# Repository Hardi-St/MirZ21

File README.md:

# MirZ21
Märklin infrared to Z21 bridge

Attention: The program is NOT released yet

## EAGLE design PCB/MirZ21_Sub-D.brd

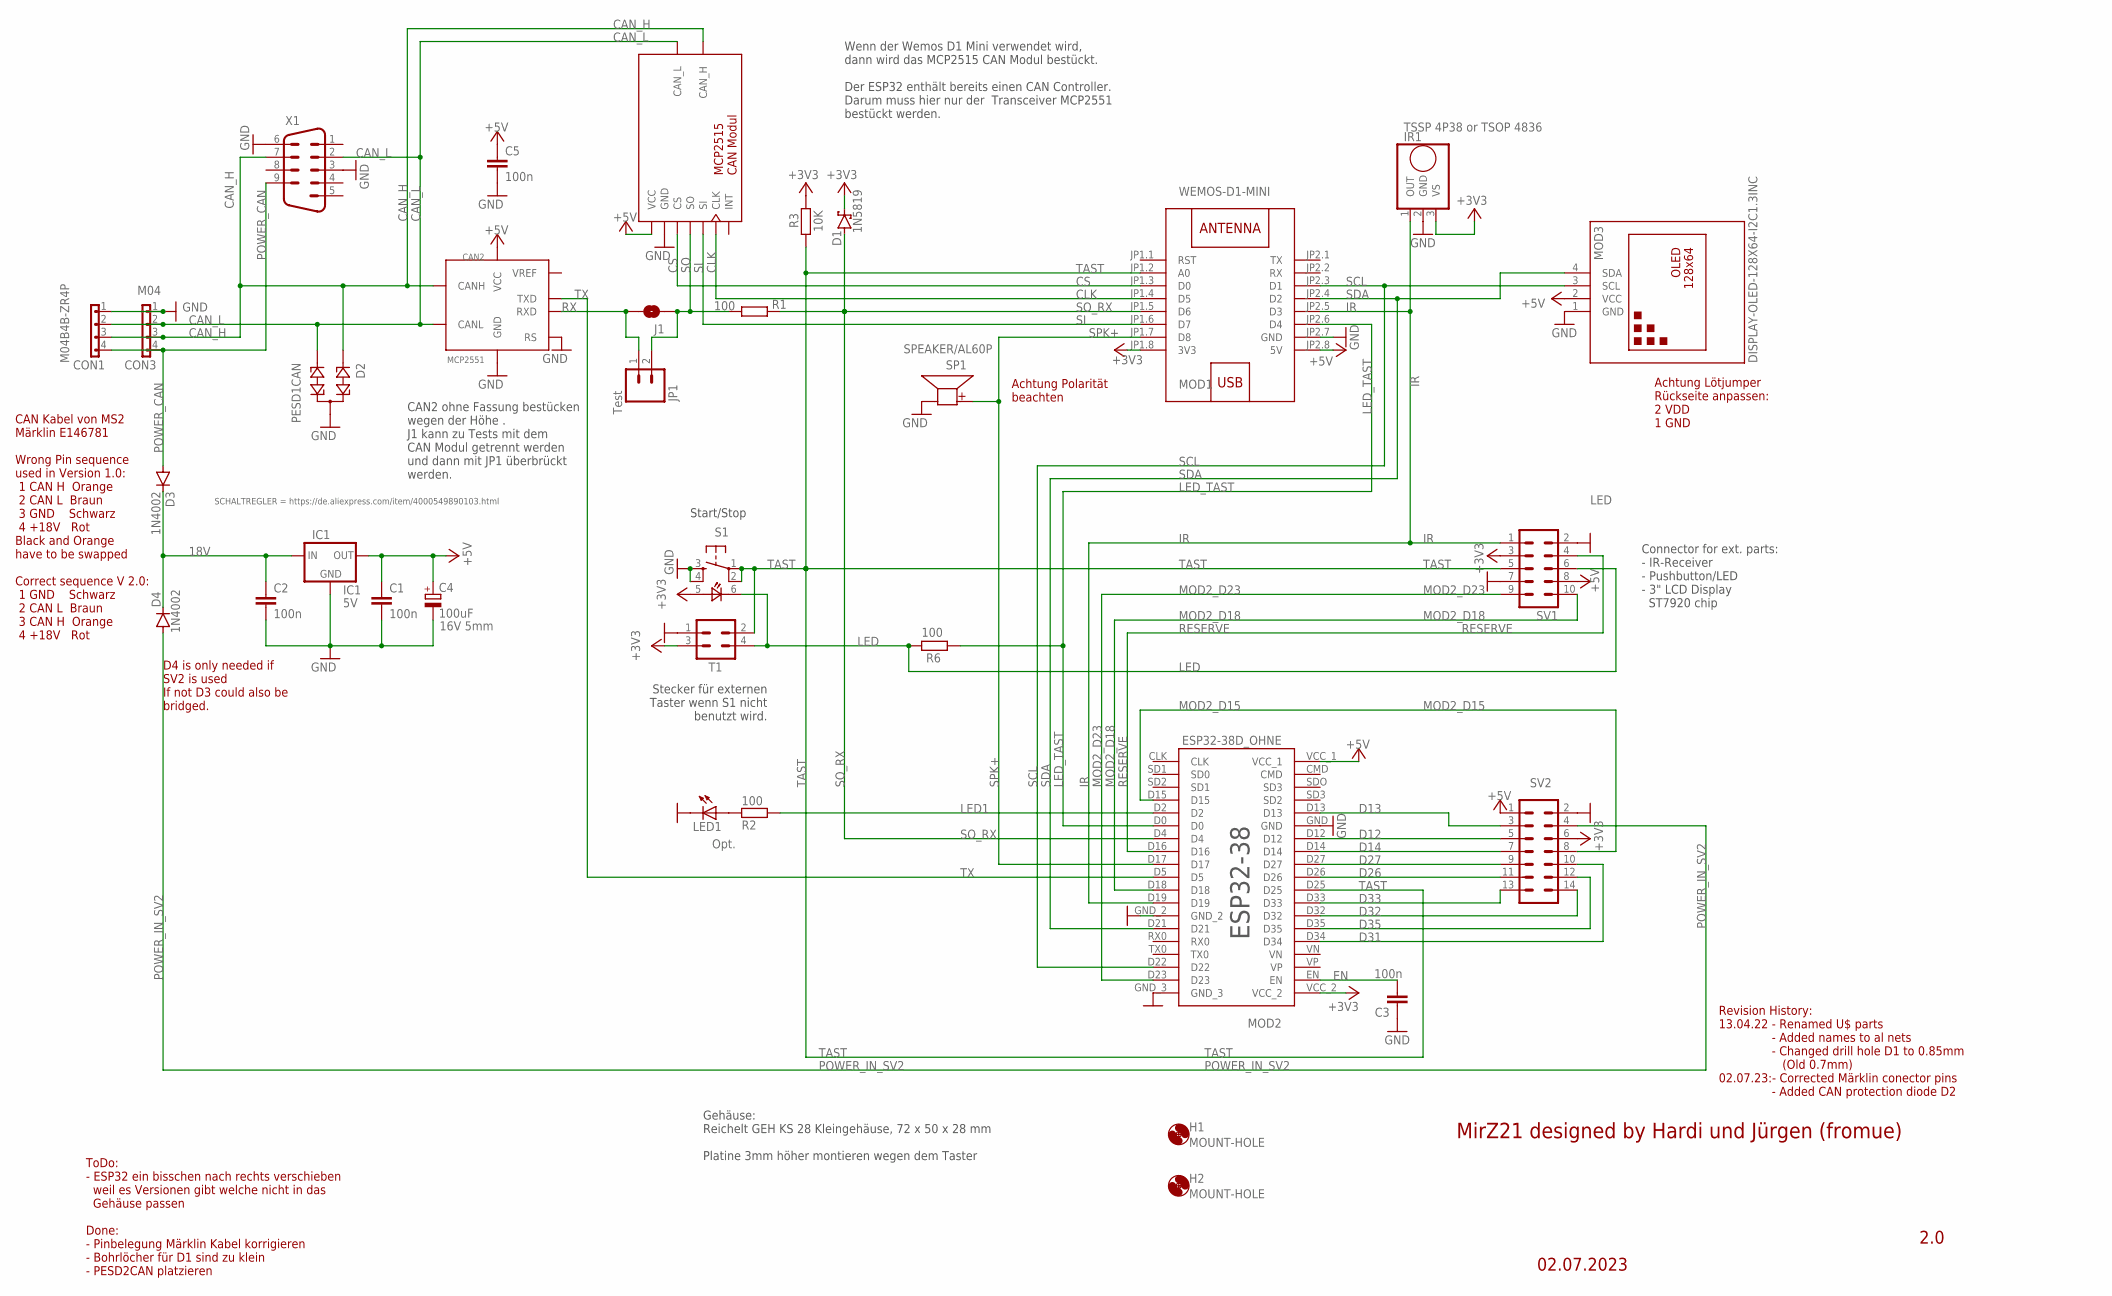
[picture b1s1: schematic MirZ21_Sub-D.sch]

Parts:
C1, C2, C3, C5: 100n; C025-025X050
C4: 100uF; TT2D5L
CAN1: MCP2515_CAN_CUTCUT; MCP2515_CAN_CUT
CAN2: MCP2551; DIP08
CON1: M04B4B-ZR4P; B4B-ZR4P
CON3: M04; 1X04
D1: 1N5819; DO41-7.6
D2: PESD1CAN; SOT23
D3, D4: 1N4002; DO41-10
H1, H2: MOUNT-HOLE; GEH_KS
IC1: 5V; HX1314G
IR1: TSSP 4P38 or TSOP 4836; TSSP4P38
J1: SOLDERJUMPERTRACE; SJ_2S-TRACE
JP1: Test; 1X02
LED1: Opt.; LED3MM
MOD1: WEMOS-D1-MINI
MOD2: ESP32-38D_OHNE; ESP32-38D_0
MOD3: DISPLAY-OLED-128X64-I2C1.3INC; DISPLAY-OLED-128X64-I2C-1.3
R1, R6: 100; 0204/7
R2: 100; 0207/2V
R3: 10K; 0204/7
S1: TASTER_LEDTC-1198-B; TASTER_LED
SP1: SPEAKER/AL60P; RMP-14SP
SV1: ML10
SV2: ML14
T1: CON-HARTING-ML_ML4ML4_FEMALE; ML_ML4_FEMALE
X1: M09D

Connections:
18V: C2.1, D3.C, D4.C, IC1.IN
+3V3: D1.C, IR1.3 (VS), MOD1.JP1.8 (3V3), MOD2.VCC_2, R3.2, S1.5 (+), SV1.3, SV2.6, T1.3
+5V: C1.1, C4.+, C5.1, CAN1.1 (VCC), CAN2.3 (VCC), IC1.OUT, MOD1.JP2.8 (5V), MOD2.VCC_1, MOD3.2 (VCC), SV1.8, SV2.1
CAN_H: CAN1.9 (CAN_H), CAN2.7 (CANH), CON1.3, CON3.3, D2.1, X1.7
CAN_L: CAN1.8 (CAN_L), CAN2.6 (CANL), CON1.2, CON3.2, D2.2, X1.2
CLK: CAN1.6 (CLK), MOD1.JP1.4 (D5)
CS: CAN1.3 (CS), MOD1.JP1.3 (D0)
D12: MOD2.D12, SV2.5
D13: MOD2.D13, SV2.3
D14: MOD2.D14, SV2.7
D26: MOD2.D26, SV2.11
D27: MOD2.D27, SV2.9
D31: MOD2.D34, SV2.10
D32: MOD2.D32, SV2.14
D33: MOD2.D33, SV2.13
D35: MOD2.D35, SV2.12
EN: C3.2, MOD2.EN
GND: C1.2, C2.2, C3.1, C4.-, C5.2, CAN1.2 (GND), CAN2.2 (GND), CAN2.8 (RS), CON1.1, CON3.1, D2.3, IC1.GND, IR1.2 (GND), LED1.K (C), MOD1.JP2.7 (GND), MOD2.GND, MOD2.GND_2, MOD2.GND_3, MOD3.1 (GND), S1.3 (S), S1.4 (S1), SP1.2 (-), SV1.2, SV1.7, SV2.2, T1.1, X1.3, X1.6
IR: IR1.1 (OUT), MOD1.JP2.5 (D3), MOD2.D19, SV1.1
LED: R6.2, S1.6 (-), SV1.6, T1.4
LED1: MOD2.D2, R2.2
LED_TAST: MOD1.JP2.6 (D4), MOD2.D0, R6.1
MOD2_D15: MOD2.D15, SV2.8
MOD2_D18: MOD2.D18, SV1.10
MOD2_D23: MOD2.D23, SV1.9
unnamed: LED1.A, R2.1
POWER_CAN: CON1.4, CON3.4, D3.A, X1.9
POWER_IN_SV2: D4.A, SV2.4
RESERVE: MOD2.D16, SV1.4
RX: CAN2.4 (RXD), J1.2, JP1.1
SCL: MOD1.JP2.3 (D1), MOD2.D22, MOD3.3 (SCL)
SDA: MOD1.JP2.4 (D2), MOD2.D21, MOD3.4 (SDA)
SI: CAN1.5 (SI), MOD1.JP1.6 (D7)
SO: CAN1.4 (SO), J1.1, JP1.2, R1.2
SO_RX: D1.A, MOD1.JP1.5 (D6), MOD2.D4, R1.1
SPK+: MOD1.JP1.7 (D8), MOD2.D17, SP1.1 (+)
TAST: MOD1.JP1.2 (A0), MOD2.D25, R3.1, S1.1, S1.2 (P1), SV1.5, T1.2
TX: CAN2.1 (TXD), MOD2.D5
VREF: CAN2.5 (VREF)

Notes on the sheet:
Achtung Polarität beachten
02.07.2023
2.0
MirZ21 designed by Hardi und Jürgen (fromue)
Start/Stop
Gehäuse: Reichelt GEH KS 28 Kleingehäuse, 72 x 50 x 28 mm Platine 3mm höher montieren wegen dem Taster
Connector for ext. parts: - IR-Receiver - Pushbutton/LED - 3" LCD Display ST7920 chip
Wenn der Wemos D1 Mini verwendet wird, dann wird das MCP2515 CAN Modul bestückt. Der ESP32 enthält bereits einen CAN Controller. Darum muss hier nur der Transceiver MCP2551 bestückt werden.
Achtung Lötjumper Rückseite anpassen: 2 VDD 1 GND
CAN2 ohne Fassung bestücken wegen der Höhe . J1 kann zu Tests mit dem CAN Modul getrennt werden und dann mit JP1 überbrückt werden.
Stecker für externen Taster wenn S1 nicht benutzt wird.
IC1
D4 is only needed if SV2 is used If not D3 could also be bridged.
Revision History: 13.04.22 - Renamed U$ parts - Added names to al nets - Changed drill hole D1 to 0.85mm (Old 0.7mm) 02.07.23:- Corrected Märklin conector pins - Added CAN protection diode D2
ToDo: - ESP32 ein bisschen nach rechts verschieben weil es Versionen gibt welche nicht in das Gehäuse passen Done: - Pinbelegung Märklin Kabel korrigieren - Bohrlöcher für D1 sind zu klein - PESD2CAN platzieren
CAN Kabel von MS2 Märklin E146781 Wrong Pin sequence used in Version 1.0: 1 CAN H Orange 2 CAN L Braun 3 GND Schwarz 4 +18V Rot Black and Orange have to be swapped Correct sequence V 2.0: 1 GND Schwarz 2 CAN L Braun 3 CAN H Orange 4 +18V Rot

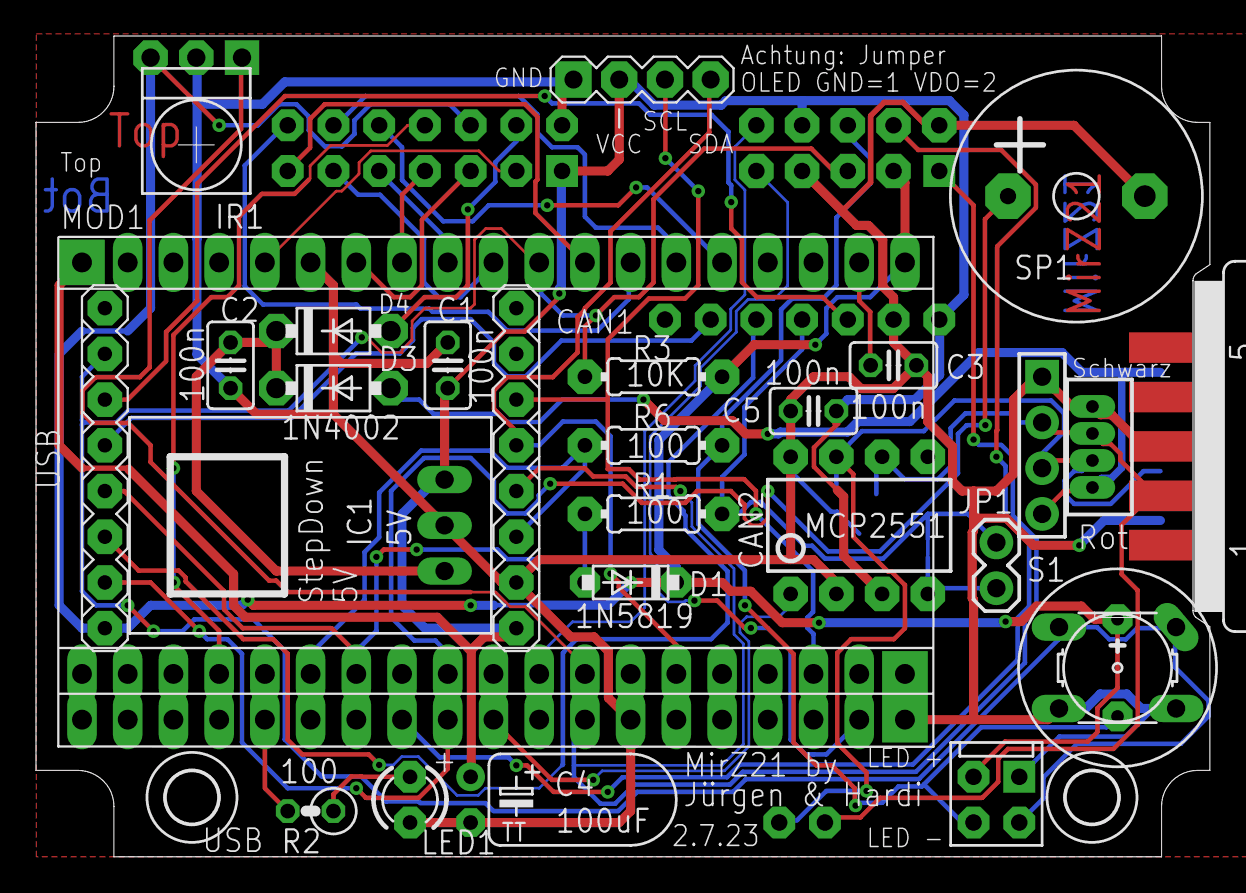
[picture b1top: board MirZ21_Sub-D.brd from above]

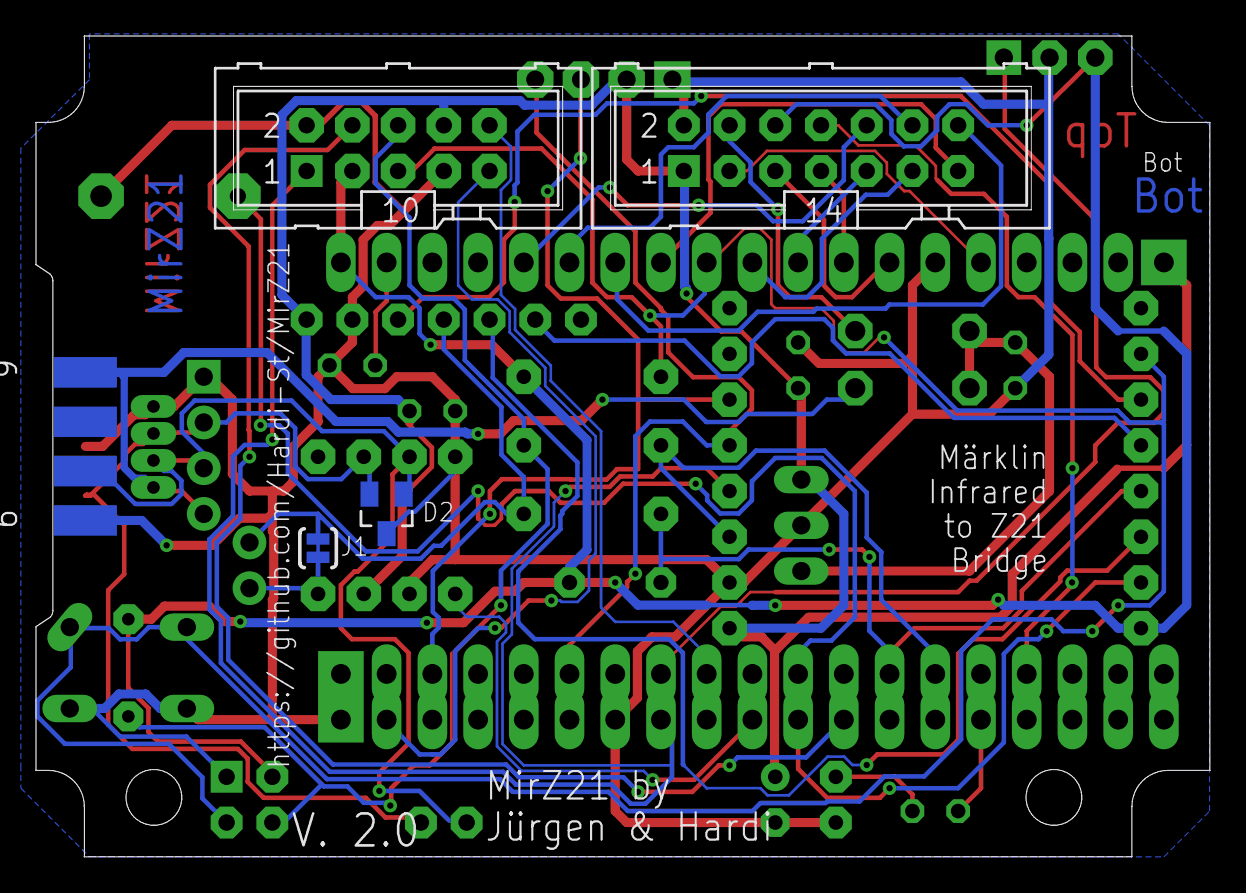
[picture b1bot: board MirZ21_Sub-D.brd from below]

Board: 2 copper layers, 65.2 x 45.6 mm, 33 parts (4 on the bottom side), 38 nets.

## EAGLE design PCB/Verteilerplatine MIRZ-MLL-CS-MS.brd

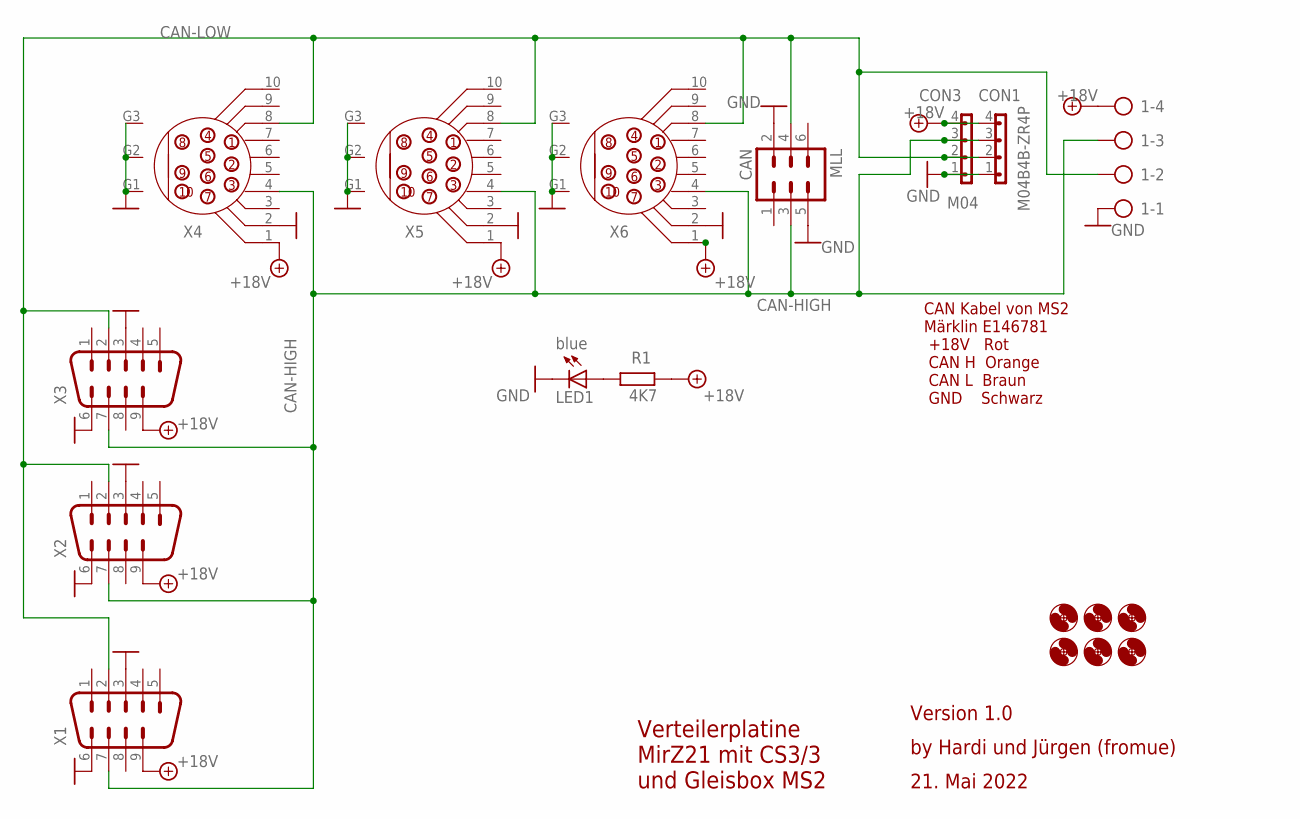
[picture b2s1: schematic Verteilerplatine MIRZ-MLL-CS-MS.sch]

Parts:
1: CAN-LOW; AK500/4-H
CON1: M04B4B-ZR4P; B4B-ZR4P
CON3: M04; 1X04
H1, H2, H3, H4, H5, H6: MOUNT-HOLE3.0; 3,0
LED1: blue; LED3MM
MLL: CAN; ML6
R1: 4K7; 0204/7
X1, X2, X3: M09V
X4, X5, X6: MDSSV-BC10; SSV-BC10

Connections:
+18V: 1.4, CON1.4, CON3.4, R1.2, X1.9, X2.9, X3.9, X4.1, X5.1, X6.1
CAN-HIGH: 1.3, CON1.3, CON3.3, MLL.3, X1.7, X2.7, X3.7, X4.4, X5.4, X6.4
CAN-LOW: 1.2, CON1.2, CON3.2, MLL.4, X1.2, X2.2, X3.2, X4.8, X5.8, X6.8
GND: 1.1, CON1.1, CON3.1, LED1.K (C), MLL.2, MLL.5, X1.3, X1.6, X2.3, X2.6, X3.3, X3.6, X4.2, X4.G1 (GND1), X4.G2 (GND2), X4.G3 (GND3), X5.2, X5.G1 (GND1), X5.G2 (GND2), X5.G3 (GND3), X6.2, X6.G1 (GND1), X6.G2 (GND2), X6.G3 (GND3)
unnamed: LED1.A, R1.1

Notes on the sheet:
CAN Kabel von MS2 Märklin E146781 +18V Rot CAN H Orange CAN L Braun GND Schwarz
Verteilerplatine MirZ21 mit CS3/3 und Gleisbox MS2
by Hardi und Jürgen (fromue)
Version 1.0
21. Mai 2022

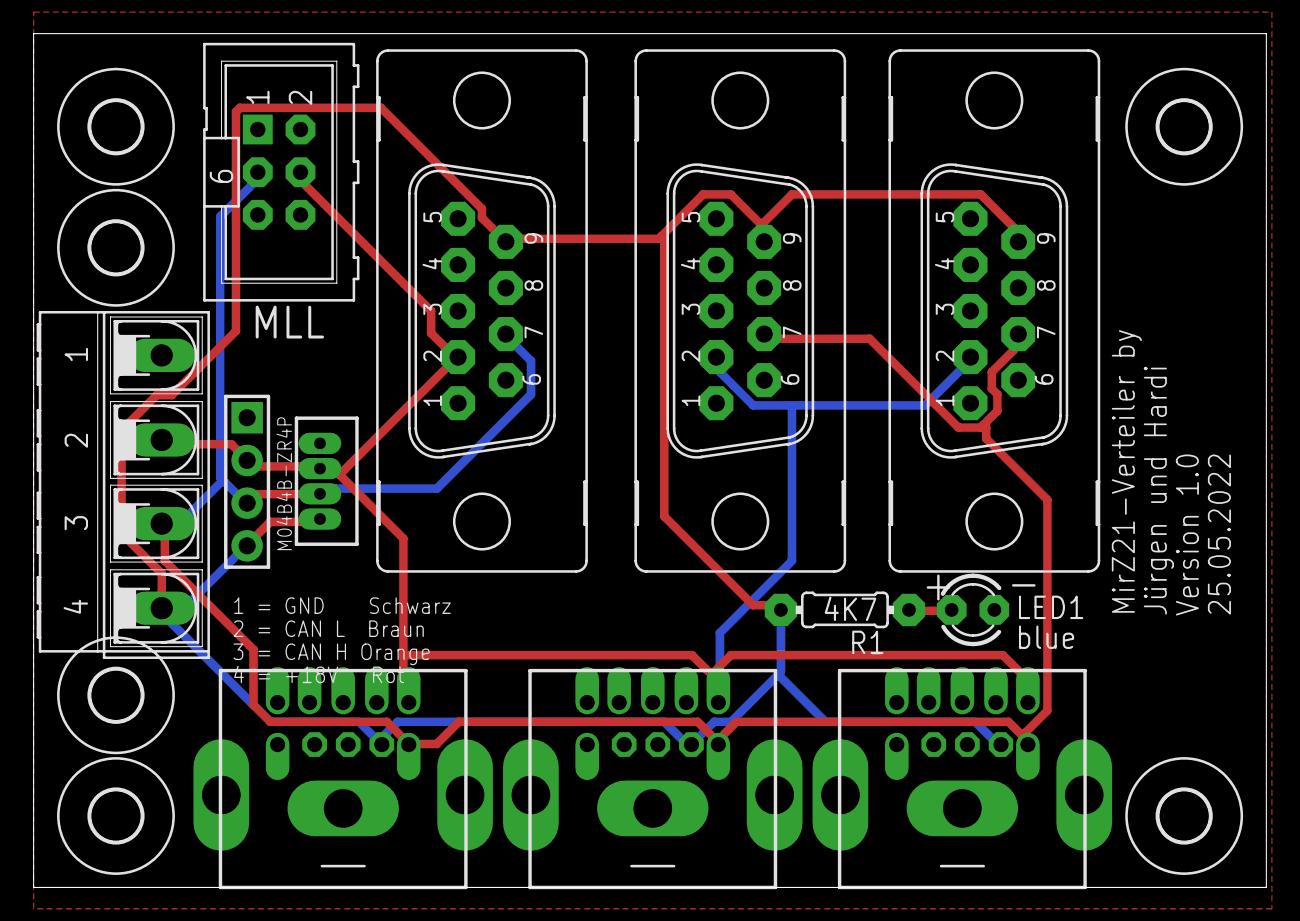
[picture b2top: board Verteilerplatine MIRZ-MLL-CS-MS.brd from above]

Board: 2 copper layers, 73.3 x 50.8 mm, 18 parts (0 on the bottom side), 5 nets.

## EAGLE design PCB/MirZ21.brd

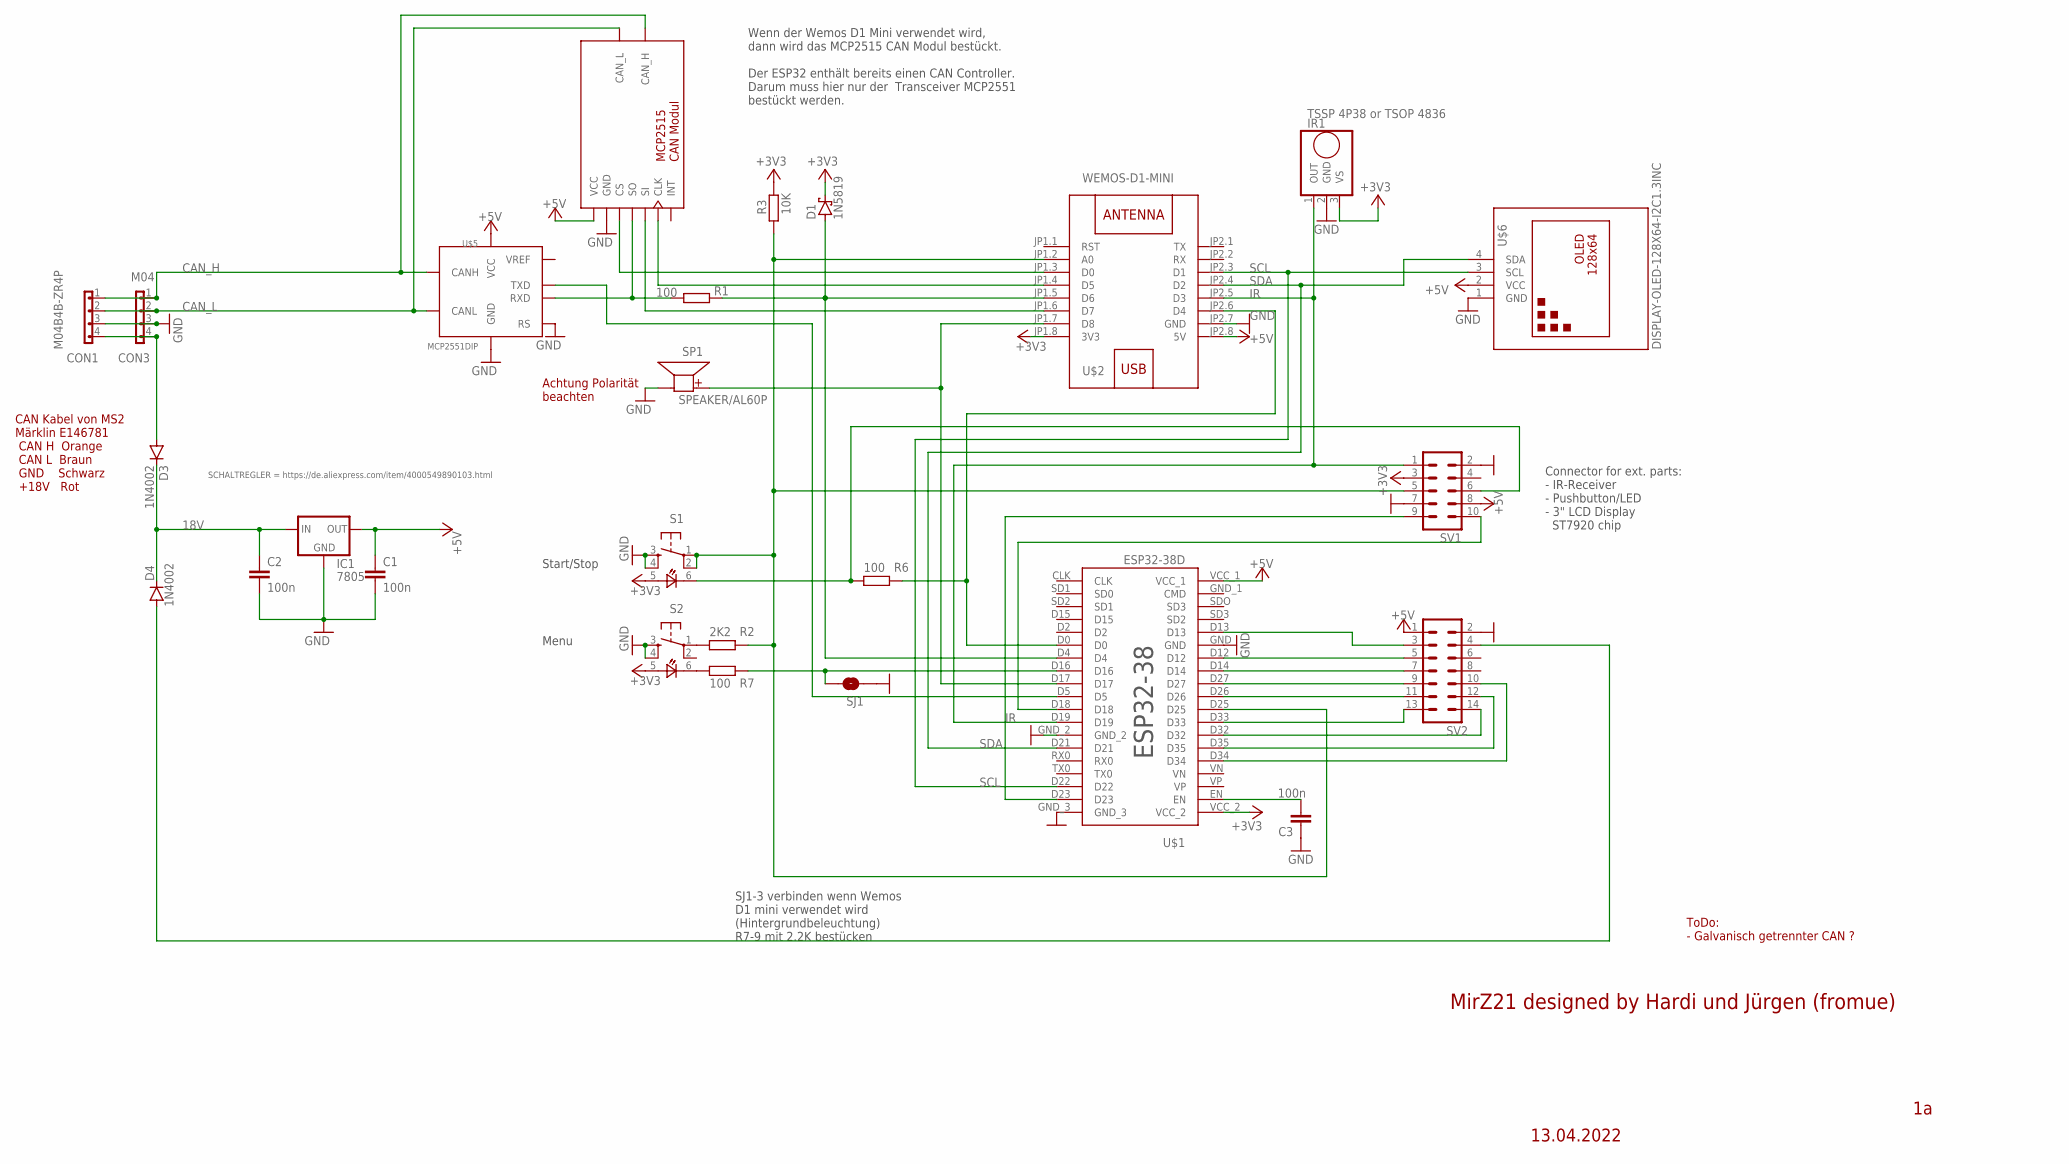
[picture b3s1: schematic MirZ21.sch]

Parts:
C1, C2, C3: 100n; C025-025X050
CAN1: MCP2515_CAN_CUTCUT; MCP2515_CAN_CUT
CON1: M04B4B-ZR4P; B4B-ZR4P
CON3: M04; 1X04
D1: 1N5819; DO41-7.6
D3, D4: 1N4002; DO41-10
IC1: 7805; HX1314G
IR1: TSSP 4P38 or TSOP 4836; TSSP4P38
R1, R6, R7: 100; 0204/7
R2: 2K2; 0204/7
R3: 10K; 0204/7
S1, S2: TASTER_LEDTC-1198-B; TASTER_LED
SJ1: SOLDERJUMPERNO; SJ_2S-NO
SP1: SPEAKER/AL60P; RMP-14SP
SV1: ML10
SV2: ML14
U$1: ESP32-38D
U$2: WEMOS-D1-MINI
U$5: MCP2551DIP; DIP08
U$6: DISPLAY-OLED-128X64-I2C1.3INC; DISPLAY-OLED-128X64-I2C-1.3

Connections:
18V: C2.1, D3.C, D4.C, IC1.IN
+3V3: D1.C, IR1.3 (VS), R3.2, S1.5 (+), S2.5 (+), SV1.3, U$1.VCC_2, U$2.JP1.8 (3V3)
+5V: C1.1, CAN1.1 (VCC), IC1.OUT, SV1.8, SV2.1, U$1.VCC_1, U$2.JP2.8 (5V), U$5.3 (VCC), U$6.2 (VCC)
CAN_H: CAN1.9 (CAN_H), CON1.1, CON3.1, U$5.7 (CANH)
CAN_L: CAN1.8 (CAN_L), CON1.2, CON3.2, U$5.6 (CANL)
GND: C1.2, C2.2, C3.1, CAN1.2 (GND), CON1.3, CON3.3, IC1.GND, IR1.2 (GND), S1.3 (S), S1.4 (S1), S2.3 (S), S2.4 (S1), SJ1.1, SP1.2 (-), SV1.2, SV1.7, SV2.2, U$1.GND, U$1.GND_2, U$1.GND_3, U$2.JP2.7 (GND), U$5.2 (GND), U$5.8 (RS), U$6.1 (GND)
IR: IR1.1 (OUT), SV1.1, U$1.D19, U$2.JP2.5 (D3)
unnamed: CAN1.3 (CS), U$2.JP1.3 (D0)
unnamed: CAN1.5 (SI), U$2.JP1.6 (D7)
unnamed: D1.A, R1.1, U$1.D4, U$2.JP1.5 (D6)
unnamed: R6.2, S1.6 (-), SV1.6
unnamed: CAN1.6 (CLK), U$2.JP1.4 (D5)
unnamed: U$1.D5, U$5.1 (TXD)
unnamed: CAN1.4 (SO), R1.2, U$5.4 (RXD)
unnamed: R7.2, S2.6 (-)
unnamed: C3.2, U$1.EN
unnamed: R2.2, S2.1
unnamed: R6.1, U$1.D0, U$2.JP2.6 (D4)
unnamed: R2.1, R3.1, S1.1, S1.2 (P1), SV1.5, U$1.D25, U$2.JP1.2 (A0)
unnamed: SP1.1 (+), U$1.D17, U$2.JP1.7 (D8)
unnamed: R7.1, SJ1.2, U$1.D16
unnamed: SV1.10, U$1.D18
unnamed: SV1.9, U$1.D23
unnamed: SV2.3, U$1.D13
unnamed: SV2.5, U$1.D12
unnamed: SV2.7, U$1.D14
unnamed: SV2.9, U$1.D27
unnamed: SV2.11, U$1.D26
unnamed: SV2.13, U$1.D33
unnamed: SV2.14, U$1.D32
unnamed: SV2.12, U$1.D35
unnamed: SV2.10, U$1.D34
unnamed: D4.A, SV2.4
unnamed: CON1.4, CON3.4, D3.A
SCL: U$1.D22, U$2.JP2.3 (D1), U$6.3 (SCL)
SDA: U$1.D21, U$2.JP2.4 (D2), U$6.4 (SDA)
VREF: U$5.5 (VREF)

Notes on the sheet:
ToDo: - Galvanisch getrennter CAN ?
Achtung Polarität beachten
CAN Kabel von MS2 Märklin E146781 CAN H Orange CAN L Braun GND Schwarz +18V Rot
13.04.2022
MirZ21 designed by Hardi und Jürgen (fromue)
Start/Stop
Menu
SJ1-3 verbinden wenn Wemos D1 mini verwendet wird (Hintergrundbeleuchtung) R7-9 mit 2.2K bestücken
Connector for ext. parts: - IR-Receiver - Pushbutton/LED - 3" LCD Display ST7920 chip
Wenn der Wemos D1 Mini verwendet wird, dann wird das MCP2515 CAN Modul bestückt. Der ESP32 enthält bereits einen CAN Controller. Darum muss hier nur der Transceiver MCP2551 bestückt werden.

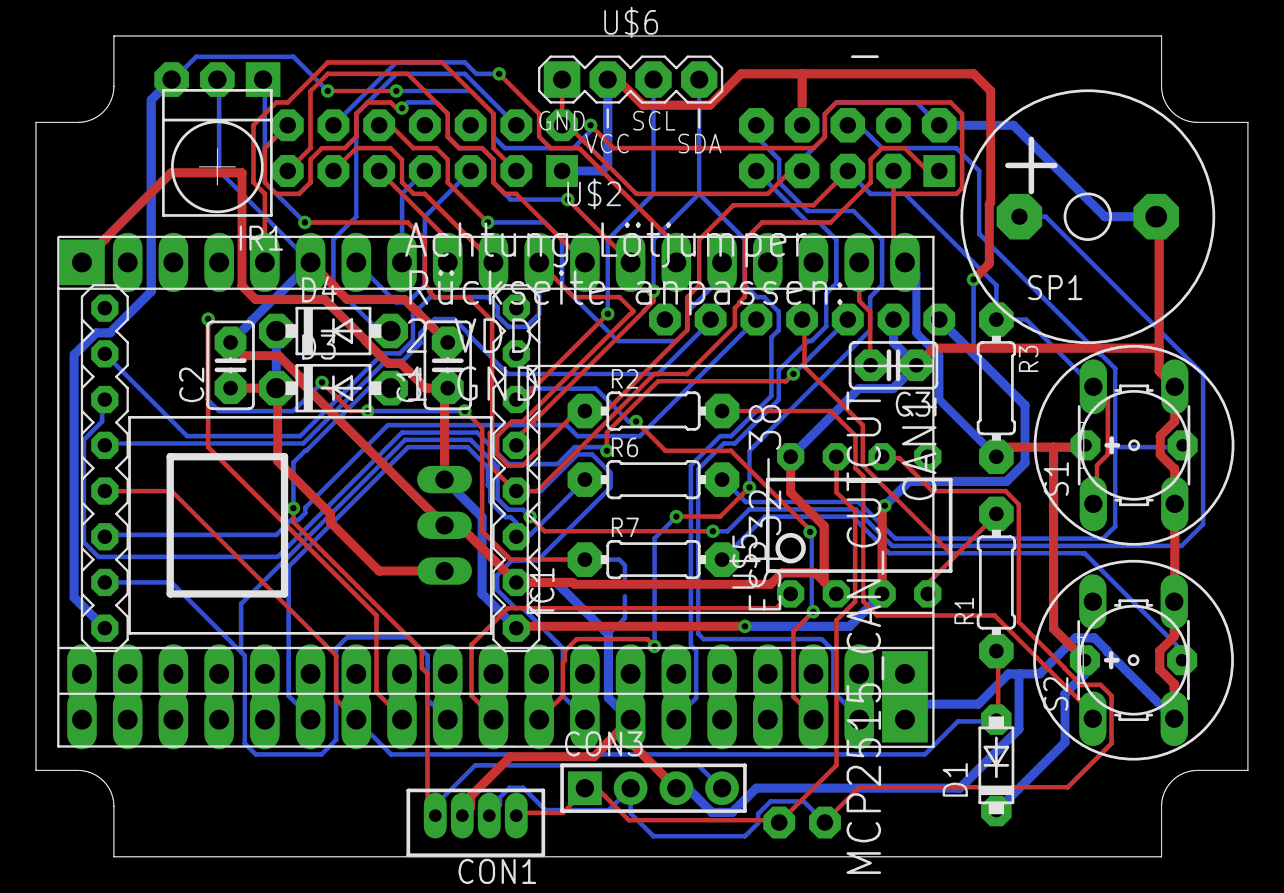
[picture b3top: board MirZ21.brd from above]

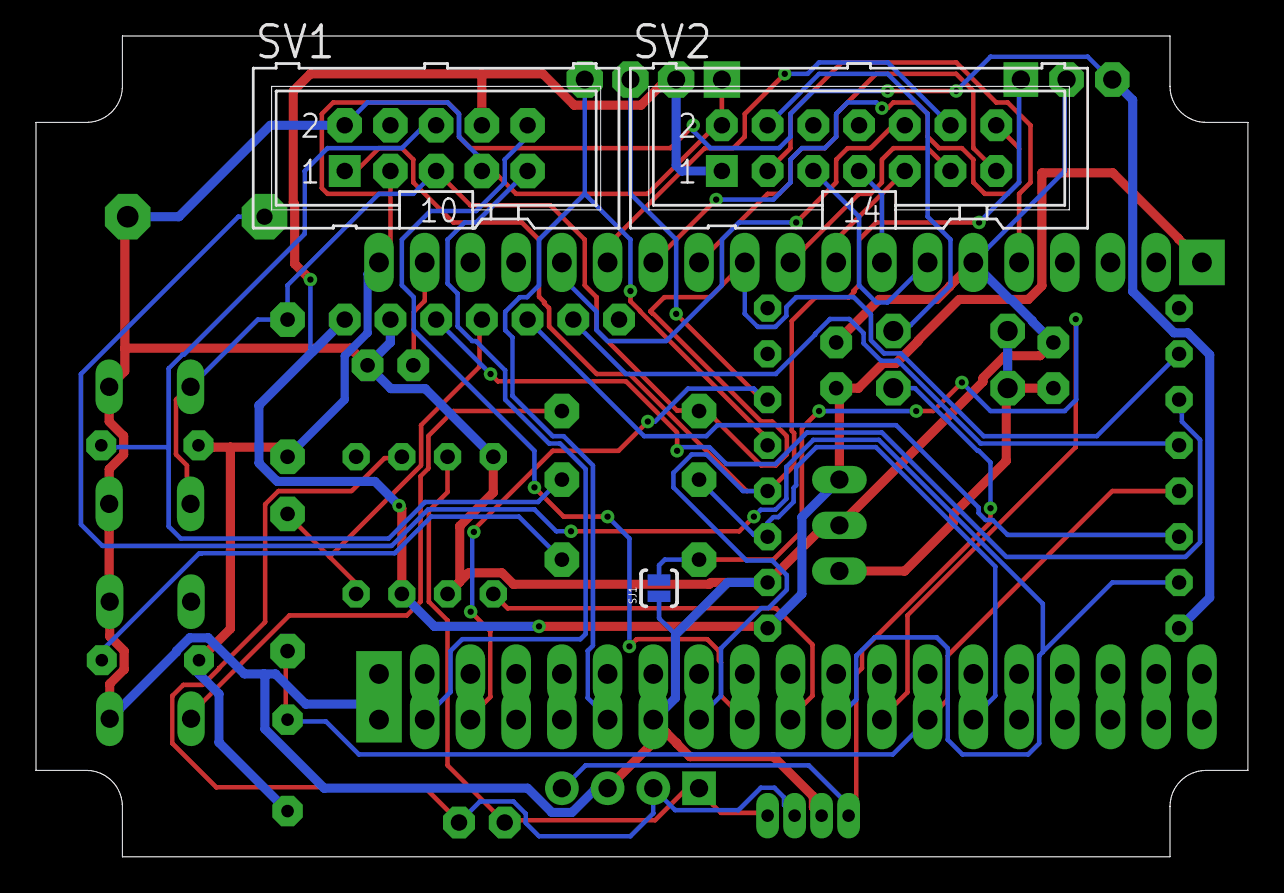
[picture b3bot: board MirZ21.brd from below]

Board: 2 copper layers, 67.3 x 45.6 mm, 26 parts (3 on the bottom side), 36 nets.

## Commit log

2022-03-09 initial
2022-03-12 German umlauts
2022-03-13 Ver 0.1
2022-03-14 Create add. locos
2022-03-18 before change of adress offset
2022-03-24 Changed adress mapping
2022-03-24 Changed adress layout
2022-03-29 New Stummi loco
2022-06-03 Added PCB/ and updated path in scripts
2022-06-03 Deleted Old PCB Version
2022-06-05 Added Verteilerplatine and next board
2022-06-24 Invert the Power LED for the ESP32
2022-07-07 Update from Juergen
    Updates 2022-07-07 12:25
    + new animations
    ~ WLAN password is no longer displayed on the configuration page
    ~ maximum number of LAN clients increased to 100
    ~ Updated ascii graphics
    ~ Updated ToDos and Lists
2022-07-14 CAN Lib which supports ESP32 chip revision >= 2
2022-07-14 Added ToDos for next revision
2022-07-14 Added new animations
2022-07-14 Several improvements
    - Fixed the CAN bus library to support the ESP32 chip revision >= 2
    - Corrected the german umlauts in the loco name display in the Maerkin IR select menu Select_Ma_Loko_Display()
    - Corrected display updating for more than 2 clients (Z21 Apps)
    - Support for WLANmouse
    - Supporting accessory commands (switches, ...)
    - - Read the lokos from the MS2/CSx if the button is pressed longer thän 5 seconds.
2022-07-14 Conflict resolving
2022-07-14 Resolving conflicts
2022-07-22 Support for accessory commands (switches..)
2022-07-23 Added Samsung BN59-01301A IR control
2023-07-02 Platine Ver. 2.0
    - Korrigierte Märklin Stecker Pins
    - CAN Schutzdiode hinzugefügt
    - Bohrloch D1 vergrößert
2023-10-18 added case for distributor
2024-04-18 Added support for new black MS2
2024-04-18 Added comments

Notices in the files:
parts and their libraries:
SparkFun-Retired: Licensing:Creative Commons ShareAlike 4.0 International - https://creativecommons.org/licenses/by-sa/4.0
diy-modules_modified_by_Hardi: Released under the Creative Commons Attribution 4.0 International License: http://creativecommons.org/licenses/by/4.0
